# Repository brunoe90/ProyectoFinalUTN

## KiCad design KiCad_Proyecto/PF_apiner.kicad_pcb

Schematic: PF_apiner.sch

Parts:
C35: 0.1uF; c_0402; Digikey# 311-1336-1-ND
D12: MBR0520; SOD-123; Digikey# MBR0520LT1GOSCT-ND
H1, H2, H3, H4: PCB_HOLE; MountingHole_3mm
J1: OBDII Header; YH1012
J2: Conn_01x05; PIN_ARRAY_5x1_1.27_SMD; Digikey# 952-3609-ND

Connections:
+5V: C35.1, D12.2; also elsewhere on the board
+5V_USB: D12.1, J2.1
/HS_CAN_N: J1.14; also elsewhere on the board
/HS_CAN_P: J1.6; also elsewhere on the board
/J1850_BUS+: J1.2; also elsewhere on the board
/J1850_BUS-: J1.10; also elsewhere on the board
/K-LINE: J1.7; also elsewhere on the board
/L-LINE: J1.15; also elsewhere on the board
/MS_CAN_N: J1.11; also elsewhere on the board
/MS_CAN_P: J1.3; also elsewhere on the board
/MicroM4/RESET: J2.4; also elsewhere on the board
/MicroM4/UART0_RX: J2.2; also elsewhere on the board
/MicroM4/UART0_TX: J2.3; also elsewhere on the board
/SW_CAN: J1.1; also elsewhere on the board
GND: C35.2, J1.4, J1.5, J2.5; also elsewhere on the board
VIN: J1.16; also elsewhere on the board

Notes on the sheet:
POWER SUPPLY
OBD II
El UART0 va al USB, el resto hay que configurarlos
agrandar d1

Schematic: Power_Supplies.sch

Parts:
C1: 10nF; c_0603
C2, C3: 0.1uF; c_0402
C4, C6, C7, C9: 47uF; c_1206
C5: 1uF; c_0402
C8: 62pF; c_0402
C10, C11: 10uF; c_0603
D1: RLCAMP0531T9; SOD-123
D2: SBR2U30P1; POWERDI-123
F1: 2A; ptc_1210; Digikey# F2570CT-ND
L1: 10uH; SRN6045
R1: 100k; r_0402
R2: 13,7k; r_0402
U1: TPS54202; SOT-23-6; Digikey# 296-44396-1-ND
U2: AZ1117EH-3.3TRG1; SOT-223

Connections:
+3.3V: C5.1, U2.2; also elsewhere on the board
+5V: C2.1, C8.1, C10.1, C11.1, L1.2, R1.1, U2.3; also elsewhere on the board
GND: C1.2, C2.2, C4.2, C5.2, C6.2, C7.2, C9.2, C10.2, C11.2, D1.1, R2.2, U1.1, U2.1; also elsewhere on the board
unnamed: C3.1, L1.1, U1.2
unnamed: C3.2, U1.6
unnamed: C8.2, R1.2, R2.1, U1.4
VIN: C1.1, F1.1; also elsewhere on the board

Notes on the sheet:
poner infinitas vias data tps #21

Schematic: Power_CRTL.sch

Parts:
Q1: 2N7002; SOT-23; Digikey# 2N7002ET1GOSCT-ND
Q2, Q3: BSS314PE; SOT-23; Digikey# BSS314PE H6327CT-ND
R3, R4: 100k; r_0402; Digikey# 311-100KLRCT-ND

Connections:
+3.3V: R3.1; also elsewhere on the board
+5V: Q3.2; also elsewhere on the board
/MicroM4/PWR_SAVE: Q1.1, R3.2; also elsewhere on the board
DLC_SW: Q2.3; also elsewhere on the board
GND: Q1.2; also elsewhere on the board
unnamed: Q1.3, Q2.1, Q3.1, R4.2

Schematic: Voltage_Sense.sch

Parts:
C12: 0.1uF; c_0402; Digikey# 311-1336-1-ND
D3: BAT54SL; SOT-23; Digikey# BAT54SLT1GOSCT-ND
R5: 62k 1%; r_0402; Digikey# 311-62.0KLRCT-ND
R6: 10K 1%; r_0402; Digikey# 311-10.0KLRCT-ND

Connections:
+3.3V: D3.2; also elsewhere on the board
/OBD_UART_Interface/ANALOG_IN: C12.1, D3.3, R5.1, R6.1; also elsewhere on the board
GND: C12.2, D3.1, R6.2; also elsewhere on the board

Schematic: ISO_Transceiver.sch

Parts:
C13, C14, C15: 0.1uF x 25V; c_0603; Digikey# 311-1341-1-ND
D4, D5: BAT54SL; SOT-23; Digikey# BAT54SLT1GOSCT-ND
Q4, Q5: MMBT3904; SOT-23; Digikey# MMBT3904LT3GOSCT-ND
R7, R13: 1K; r_0402; Digikey# 311-1.0KJRCT-ND
R8, R9, R11, R12: 10K; r_0402; Digikey# 311-10KJRCT-ND
R10, R14: 510 0.5W; r_0805; Digikey# P510ADCT-ND
U3: LM339; TSSOP-14_4.4x5mm_Pitch0.65mm; Digikey# 296-6607-1-ND

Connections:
+3.3V: R12.2; also elsewhere on the board
/ISO_Transceiver/ISO_K_TX: R7.1; also elsewhere on the board
/ISO_Transceiver/ISO_L_TX: R13.1; also elsewhere on the board
/ISO_Transceiver/ISO_RX: R12.1, U3.2; also elsewhere on the board
/K-LINE: D4.3, Q4.3, R10.1, R11.1; also elsewhere on the board
/L-LINE: D5.3, Q5.3, R14.1; also elsewhere on the board
DLC_SW: C15.1, R8.2, R10.2, R14.2, U3.3 (V+); also elsewhere on the board
GND: C13.2, C14.2, C15.2, D4.1, D5.1, Q4.2, Q5.2, R9.1, U3.12 (V-); also elsewhere on the board
unnamed: Q4.1, R7.2
unnamed: Q5.1, R13.2
unnamed: R8.1, R9.2, U3.5 (+)
unnamed: R11.2, U3.4 (-)

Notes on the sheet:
Ubicar cerca del LM339

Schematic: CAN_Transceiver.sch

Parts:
C16, C17: 0.1uF; c_0402; Digikey# 311-1336-1-ND
C18: 10uF 25V; c_0805; Digikey# 587-2985-6-ND
C19, C20, C22, C23: 560 pF; c_0402; Digikey# 311-1029-1-ND
C21: 150 pF; c_0402; Digikey# 490-3229-1-ND
Q6: 2N7002; SOT-23; Digikey# 2N7002ET1GOSCT-ND
R15: 1,5K; r_0402; Digikey# 311-1.50KLRCT-ND
R16: 6,49K; r_0805; Digikey# 311-6.49KCRCT-ND
R17, R19, R22, R24: 100; r_0402; Digikey# 311-100JRCT-ND
R18: 10K; r_0402; Digikey# 311-10KJRCT-ND
R20: 130; r_2512; Digikey# A116011CT-ND
R21, R23: DNP; c_0402; Digikey# 311-120JRCT-ND
U4: MCP25612FD; SOIC-14; Digikey# MCP25612FD-H/SL-ND
U5: TH8056; SOIC-8; Digikey# TH8056KDC-AAA-008-RETR-ND
U6, U7, U8: PESD1CAN; SC-70; Digikey# 568-10731-1-ND

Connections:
+3.3V: R15.2; also elsewhere on the board
/CAN_Transceiver/HS_CAN_RX: U4.4; also elsewhere on the board
/CAN_Transceiver/HS_CAN_TX: U4.1; also elsewhere on the board
/CAN_Transceiver/MS_CAN_RX: U4.8; also elsewhere on the board
/CAN_Transceiver/MS_CAN_TX: U4.5; also elsewhere on the board
/CAN_Transceiver/SW_CAN_LOAD: Q6.1, R18.2; also elsewhere on the board
/CAN_Transceiver/SW_CAN_MODE0: U5.2; also elsewhere on the board
/CAN_Transceiver/SW_CAN_MODE1: U5.3; also elsewhere on the board
/CAN_Transceiver/SW_CAN_RX: R15.1, U5.4; also elsewhere on the board
/CAN_Transceiver/SW_CAN_TX: U5.1; also elsewhere on the board
/HS_CAN_N: R19.2, R21.2, U4.12, U6.1; also elsewhere on the board
/HS_CAN_P: R17.2, R21.1, U4.13, U6.2; also elsewhere on the board
/MS_CAN_N: R23.2, R24.2, U4.9, U8.2; also elsewhere on the board
/MS_CAN_P: R22.2, R23.1, U4.10, U8.1; also elsewhere on the board
/SW_CAN: C21.1, R16.2, R20.2, U5.7, U7.1, U7.2; also elsewhere on the board
GND: C16.1, C17.1, C18.2, C19.2, C20.2, C21.2, C22.2, C23.2, Q6.2, R18.1, U4.2, U4.6, U4.11, U4.14, U5.8, U6.3, U7.3, U8.3; also elsewhere on the board
unnamed: C19.1, R17.1
unnamed: C20.1, R19.1
unnamed: C22.1, R22.1
unnamed: C23.1, R24.1
unnamed: Q6.3, R20.1
unnamed: R16.1, U5.6

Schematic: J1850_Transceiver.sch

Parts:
C24, C25, C26, C27: 0.1uF x 25V; c_0603; Digikey# 311-1341-1-ND
D6, D7: BAT54SL; SOT-23; Digikey# BAT54SLT1GOSCT-ND
D8, D9, D10: DB2J31000L; SOD-323; Digikey# DB2J31000LCT-ND
Q7, Q8, Q10: 2N7002; SOT-23; Digikey# 2N7002ET1GOSCT-ND
Q9: BSS314PE; SOT-23; Digikey# BSS314PE H6327CT-ND
R25: 240; r_0402; Digikey# 311-240LRCT-ND
R26: 866; r_0402; Digikey# YAG3248CT-ND
R27: 374; r_0402; Digikey# YAG3137CT-ND
R28, R29, R30, R31, R32, R33, R35, R36, R37, R38, R39: 10K; r_0402; Digikey# 311-10KJRCT-ND
R34: 2,7K; r_0402; Digikey# 311-2.7KJRCT-ND
U3: LM339; TSSOP-14_4.4x5mm_Pitch0.65mm; Digikey# 296-6607-1-ND
U9: LM317; SOT-89-3; Digikey# 296-26093-1-ND

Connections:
+3.3V: R33.2, R39.2; also elsewhere on the board
/J1850_BUS+: D6.3, D8.2, R30.1, R32.2, R37.1; also elsewhere on the board
/J1850_BUS-: D7.3, Q10.3, R31.1, R38.1; also elsewhere on the board
/J1850_Transceiver/J1850_BUS+_TX: Q8.1, R28.2; also elsewhere on the board
/J1850_Transceiver/J1850_BUS+_VH: Q7.1; also elsewhere on the board
/J1850_Transceiver/J1850_BUS-_TX: Q10.1, R36.1; also elsewhere on the board
/J1850_Transceiver/PWM_RX: R33.1, U3.1; also elsewhere on the board
/J1850_Transceiver/VPW_RX: R39.1, U3.13; also elsewhere on the board
DLC_SW: C25.1, U3.3 (V+), U9.3; also elsewhere on the board
GND: C24.2, C25.2, C26.2, C27.2, D6.1, D7.1, D9.2, Q7.2, Q8.2, Q10.2, R27.1, R28.1, R35.1, U3.12 (V-); also elsewhere on the board
unnamed: D8.1, Q9.3
unnamed: D9.1, R32.1
unnamed: D10.2, R38.2
unnamed: Q7.3, R26.1, R27.2
unnamed: Q8.3, Q9.1, R29.1
unnamed: R25.1, R26.2, U9.1
unnamed: R30.2, U3.7 (+)
unnamed: R31.2, U3.6 (-)
unnamed: R34.1, R35.2, U3.10 (-)
unnamed: R37.2, U3.11 (+)

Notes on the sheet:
revizar este footprint

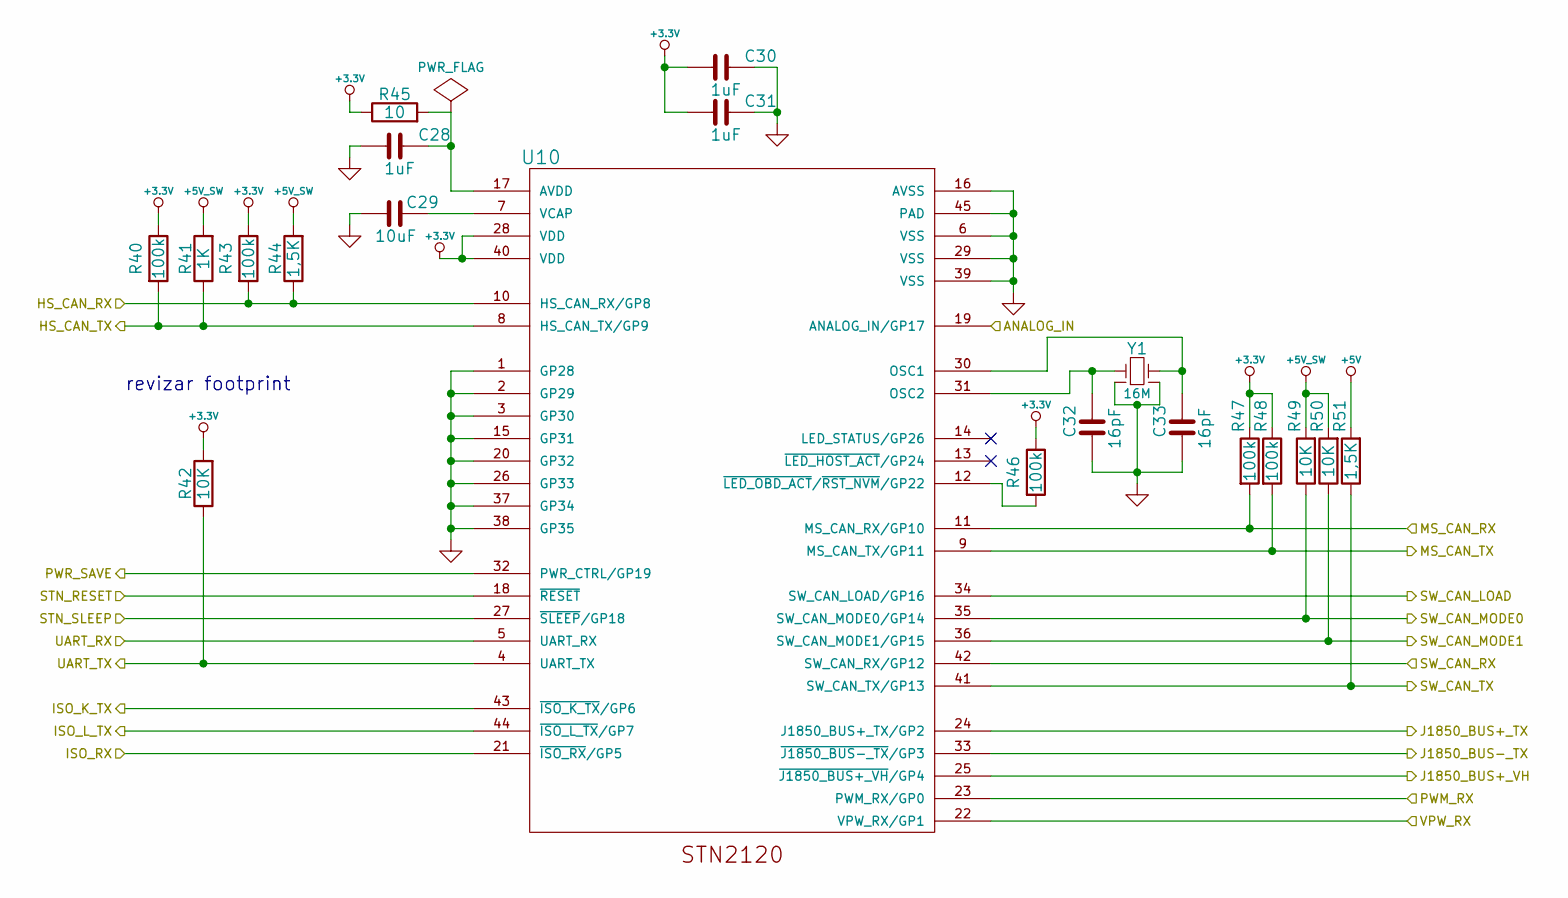
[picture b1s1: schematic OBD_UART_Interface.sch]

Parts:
C28, C30, C31: 1uF; c_0402; Digikey# 587-1231-1-ND
C29: 10uF; c_0603; Digikey# 587-1256-1-ND
C32, C33: 16pF; c_0402; Digikey# 490-5926-1-ND
R40, R43, R46, R47, R48: 100k; r_0402; Digikey# 311-100KLRCT-ND
R41: 1K; r_0402; Digikey# 311-1.0KJRCT-ND
R42: 10K; r_0402; Digikey# 311-1.0KJRCT-ND
R44, R51: 1,5K; r_0402; Digikey# 311-1.50KLRCT-ND
R45: 10; r_0402; Digikey# 311-10JRCT-ND
R49, R50: 10K; r_0402; Digikey# 311-10KJRCT-ND
U10: STN2120; QFN-44-1EP_8x8mm_Pitch0.65mm
Y1: 16M; XTAL_32x25; Digikey# 887-2555-1-ND

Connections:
+3.3V: C30.2, C31.2, R40.1, R42.2, R43.1, R45.1, R46.1, R47.1, R48.1, U10.28 (VDD), U10.40 (VDD); also elsewhere on the board
+5V: R51.2; also elsewhere on the board
/CAN_Transceiver/HS_CAN_RX: R43.2, R44.1, U10.10 (HS_CAN_RX/GP8); also elsewhere on the board
/CAN_Transceiver/HS_CAN_TX: R40.2, R41.1, U10.8 (HS_CAN_TX/GP9); also elsewhere on the board
/CAN_Transceiver/MS_CAN_RX: R47.2, U10.11 (MS_CAN_RX/GP10); also elsewhere on the board
/CAN_Transceiver/MS_CAN_TX: R48.2, U10.9 (MS_CAN_TX/GP11); also elsewhere on the board
/CAN_Transceiver/SW_CAN_LOAD: U10.34 (SW_CAN_LOAD/GP16); also elsewhere on the board
/CAN_Transceiver/SW_CAN_MODE0: R49.1, U10.35 (SW_CAN_MODE0/GP14); also elsewhere on the board
/CAN_Transceiver/SW_CAN_MODE1: R50.1, U10.36 (SW_CAN_MODE1/GP15); also elsewhere on the board
/CAN_Transceiver/SW_CAN_RX: U10.42 (SW_CAN_RX/GP12); also elsewhere on the board
/CAN_Transceiver/SW_CAN_TX: R51.1, U10.41 (SW_CAN_TX/GP13); also elsewhere on the board
/ISO_Transceiver/ISO_K_TX: U10.43 (~ISO_K_TX~/GP6); also elsewhere on the board
/ISO_Transceiver/ISO_L_TX: U10.44 (~ISO_L_TX~/GP7); also elsewhere on the board
/ISO_Transceiver/ISO_RX: U10.21 (~ISO_RX~/GP5); also elsewhere on the board
/J1850_Transceiver/J1850_BUS+_TX: U10.24 (J1850_BUS+_TX/GP2); also elsewhere on the board
/J1850_Transceiver/J1850_BUS+_VH: U10.25 (~J1850_BUS+_VH~/GP4); also elsewhere on the board
/J1850_Transceiver/J1850_BUS-_TX: U10.33 (~J1850_BUS-_TX~/GP3); also elsewhere on the board
/J1850_Transceiver/PWM_RX: U10.23 (PWM_RX/GP0); also elsewhere on the board
/J1850_Transceiver/VPW_RX: U10.22 (VPW_RX/GP1); also elsewhere on the board
/MicroM4/PWR_SAVE: U10.32 (PWR_CTRL/GP19); also elsewhere on the board
/MicroM4/STN_RESET: U10.18 (~RESET); also elsewhere on the board
/MicroM4/STN_SLEEP: U10.27 (~SLEEP~/GP18); also elsewhere on the board
/MicroM4/UART1_RX: R42.1, U10.4 (UART_TX); also elsewhere on the board
/MicroM4/UART1_TX: U10.5 (UART_RX); also elsewhere on the board
/OBD_UART_Interface/ANALOG_IN: U10.19 (ANALOG_IN/GP17); also elsewhere on the board
GND: C28.2, C29.1, C30.1, C31.1, C32.2, C33.2, U10.1 (GP28), U10.2 (GP29), U10.3 (GP30), U10.6 (VSS), U10.15 (GP31), U10.16 (AVSS), U10.20 (GP32), U10.26 (GP33), U10.29 (VSS), U10.37 (GP34), U10.38 (GP35), U10.39 (VSS), U10.45 (PAD), Y1.2, Y1.4; also elsewhere on the board
unnamed: C28.1, R45.2, U10.17 (AVDD)
unnamed: C29.2, U10.7 (VCAP)
unnamed: C32.1, U10.31 (OSC2), Y1.1
unnamed: C33.1, U10.30 (OSC1), Y1.3
unnamed: R46.2, U10.12 (~LED_OBD_ACT~/~RST_NVM~/GP22)

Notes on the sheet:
revizar footprint

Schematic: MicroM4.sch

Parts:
C34, C37, C38: 0.1uF; c_0402; Digikey# 311-1336-1-ND
C36: 10uF; c_0603; Digikey# 587-1256-1-ND
DS1: LED; LED-0603; Digikey# SML-D12U1WT86CT-ND
R52, R54: 10K; r_0402; Digikey# 311-10KJRCT-ND
R53: 100K; l_0402; Digikey# MCS0402-100K-CFCT-ND
R55: 100; r_0402; Digikey# 311-100JRCT-ND
SW1: SW_RESET; TACT_SMD_4.5X4.5; Digikey# EG5350CT-ND
SW2: SW_BOOT; TACT_SMD_4.5X4.5; Digikey# EG5350CT-ND
U14: ESP32-WROOM; Digikey# 1904-1023-1-ND

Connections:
+3.3V: C36.1, C37.1, R52.2, R53.1, R54.2, U14.2; also elsewhere on the board
/MicroM4/BOOT: C34.1, R54.1, SW2.1, SW2.2, U14.25
/MicroM4/Led_Status: R55.2, U14.13
/MicroM4/PWR_SAVE: U14.28; also elsewhere on the board
/MicroM4/RESET: C38.1, R52.1, SW1.1, SW1.2, U14.3; also elsewhere on the board
/MicroM4/STN_RESET: U14.10; also elsewhere on the board
/MicroM4/STN_SLEEP: U14.33; also elsewhere on the board
/MicroM4/UART0_RX: R53.2, U14.34; also elsewhere on the board
/MicroM4/UART0_TX: U14.35; also elsewhere on the board
/MicroM4/UART1_RX: U14.17; also elsewhere on the board
/MicroM4/UART1_TX: U14.18; also elsewhere on the board
GND: C34.2, C38.2, DS1.2 (A), SW1.3, SW1.4, SW2.3, SW2.4, U14.1, U14.14, U14.15, U14.24, U14.38, U14.39; also elsewhere on the board
unnamed: C36.2, C37.2
unnamed: DS1.1 (K), R55.1

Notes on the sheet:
PAG 10 pull-up interno GPIO 0 -> 0: DOWNLOAD BOOT GPIO 0 -> 1: SPI BOOT
PAG 10 GPIO15 -> MTDO-> 0 -> U0TXD Silent dejarlo sin soldar la resistencia y despues poner una de 0 ohm
PAG 15 Figure 5 GPIO12 -> MTDI ->0

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
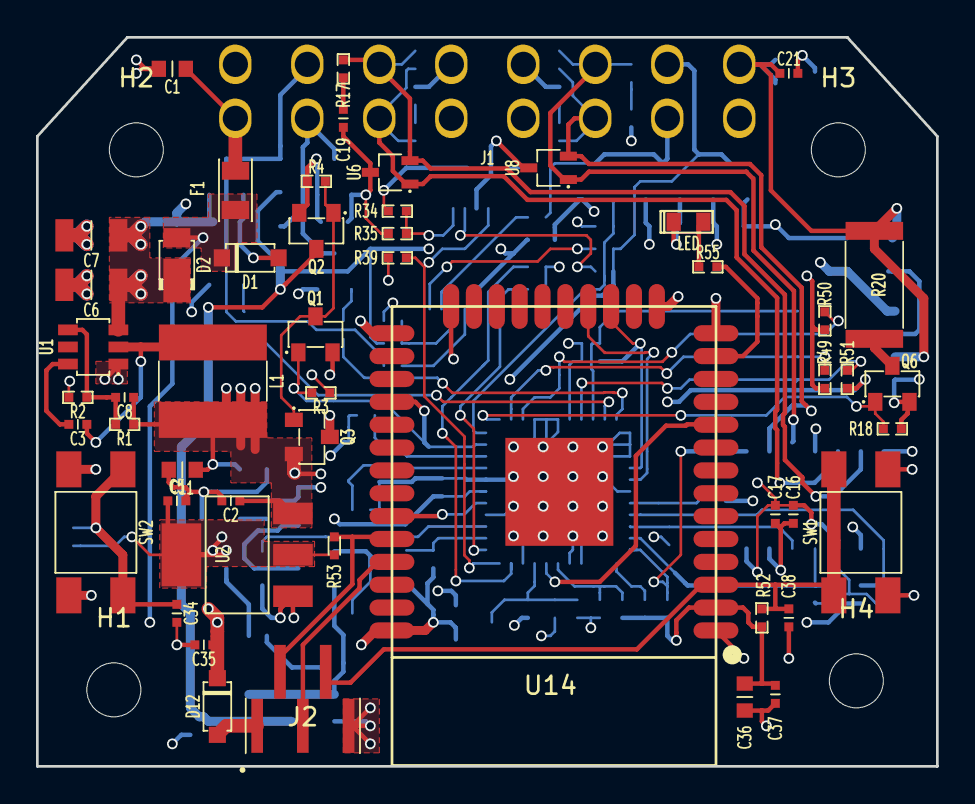
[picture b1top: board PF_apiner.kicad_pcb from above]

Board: 4 copper layers, 50.0 x 40.5 mm, 137 parts (0 on the bottom side), 78 nets.

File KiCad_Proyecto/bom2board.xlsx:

Prj: | PF_apiner.xml |  |  |  |  |  | Board Qty: | 5
Co.: |  |  |  |  |  |  | Unit Cost: | 0
Prj date: | dom 11 ago 2019 18:53:19 -03 |  |  |  |  |  | Total Cost: | 0
$ date: | 2019-08-12 21:58:06
Global Part Info
Refs | Value | Desc | Footprint | Manf | Manf# | Qty | Unit$ | Ext$
C1 | 10nF | CAP CER 10000PF 25V C0G 0603 | chip_rlc:c_0603 | TDK Corporation | 445-2664-1-ND | 5 |  | 0
C10,C11 | 10uF | CAP CER 10UF 6.3V X5R 0603 | chip_rlc:c_0603 | Taiyo Yuden | 587-1256-1-ND | 10 |  | 0
C12,C16,C17,C34,C35,C37,C38 | 0.1uF | CAP CER 0.1UF 10V X5R 0402 | chip_rlc:c_0402 | Yageo | CC0402KRX5R6BB104 | 35 |  | 0
C18 | 10uF 25V | CAP CER 10UF 25V X5R 0805 | chip_rlc:c_0805 | Taiyo Yuden | TMK212BBJ106KG-T | 5 |  | 0
C19,C20,C22,C23 | 560 pF | CAP CER 560PF 50V X7R 0402 | chip_rlc:c_0402 | Yageo | CC0402KRX7R9BB561 | 20 |  | 0
C2,C3 | 0.1uF | CAP CER 0.1UF 10V X5R 0402 | chip_rlc:c_0402 | Yageo | 311-1336-1-ND | 10 |  | 0
C21 | 150 pF | CAP CER 150PF 50V C0G/NP0 0402 | chip_rlc:c_0402 | Murata | GRM1555C1H151JA01D | 5 |  | 0
C28,C30,C31 | 1uF | CAP CER 1UF 6.3V X5R 0402 | chip_rlc:c_0402 | Taiyo Yuden | JMK105BJ105KV-F | 15 |  | 0
C29,C36 | 10uF | CAP CER 10UF 6.3V X5R 0603 | chip_rlc:c_0603 | Taiyo Yuden | JMK107BJ106MA-T | 10 |  | 0
C32,C33 | 16pF | CAP CER 16PF 50V C0G/NP0 0402 | chip_rlc:c_0402 | Murata | GRM1555C1H160JA01D | 10 |  | 0
C4,C6,C7,C9 | 47uF | 47µF ±20% 25V Ceramic Capacitor X5R 1206 (3216 Metric) | chip_rlc:c_1206 | TDK Corporation | 445-8047-1-ND | 20 |  | 0
C5 | 1uF | CAP CER 1UF 6.3V X5R 0402 | chip_rlc:c_0402 | Taiyo Yuden | 587-1231-1-ND | 5 |  | 0
C8 | 62pF | CAP CER 62PF 50V C0G/NPO 0402 | chip_rlc:c_0402 | Yageo | 311-1674-1-ND | 5 |  | 0
C13-C15,C24-C27 | 0.1uF x 25V | CAP CER 0.1UF 25V X7R 0603 | chip_rlc:c_0603 | Yageo | CC0603KRX7R8BB104 | 35 |  | 0
D1 | RLCAMP0531T9 | TVS DIODE 14VWM 23.2VC SOD-123FL | to-sod-sot:SOD-123 | Micro Commercial Co | SMF14A-TPMSCT-ND | 5 |  | 0
D12 | MBR0520 | DIODE SCHOTTKY 20V 500MA SOD123 | to-sod-sot:SOD-123 | ON Semiconductor | MBR0520LT1G | 5 |  | 0
D2 | SBR2U30P1 | DIODE SBR 30V 2A POWERDI123 | to-sod-sot:POWERDI-123 | Diodes Incorporated | SBR2U30P1DICT-ND | 5 |  | 0
D3-D7 | BAT54SL | Diode Array 1 Pair Series Connection Schottky 30V 200mA (DC) Surface Mount TO-2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 | to-sod-sot:SOT-23 | ON Semiconductor | BAT54SLT1G | 25 |  | 0
D8-D10 | DB2J31000L | Diode Schottky 30V 200mA Surface Mount SMini2-F5-B | to-sod-sot:SOD-323 | Panasonic Electronic Components | DB2J31000L | 15 |  | 0
DS1 | LED |  | misc:LED-0603 | Rohm Semiconductor | SML-D12U1WT86 | 5 |  | 0
F1 | 2A | FUSE BOARD MNT 2A 63VAC/VDC 1206 | misc:ptc_1210 | Littelfuse Inc. | 0468002.NR | 5 |  | 0
H1-H4 | PCB_HOLE |  | misc:MountingHole_3mm |  |  | 20 |  | 0
J1 | OBDII Header | OBDII male 90° connector | conn:YH1012 | Yeahui | YH1012 | 5 |  | 0
J2 | Conn_01x05 | CONN HDR 1.27MM SMT AU 5POS | conn:PIN_ARRAY_5x1_1.27_SMD | Harwin Inc. | M50-3630542 | 5 |  | 0
L1 | 10uH | 10µH Shielded Wirewound Inductor 2.5A 58.6 mOhm Max Nonstandard | inductor:SRN6045 | Bourns Inc | SRN6045-100MCT-ND | 5 |  | 0
Q1,Q6-Q8,Q10 | 2N7002 | MOSFET N-CH 60V 260MA SOT-23 | to-sod-sot:SOT-23 | ON Semiconductor | 2N7002ET1G | 25 |  | 0
Q2,Q3,Q9 | BSS314PE | MOSFET P-CH 30V 1.5A SOT23 | to-sod-sot:SOT-23 | Infineon | BSS314PE H6327 | 15 |  | 0
Q4,Q5 | MMBT3904 | TRANS NPN 40V 0.2A SOT23 | to-sod-sot:SOT-23 | ON Semiconductor | MMBT3904LT3G | 10 |  | 0
R1 | 100k | RES SMD 100K OHM 1% 1/16W 0402 | chip_rlc:r_0402 | Yageo | 311-100KLRCT-ND | 5 |  | 0
R10,R14 | 510 0.5W | RES SMD 510 OHM 5% 1/2W 0805 | chip_rlc:r_0805 | Panasonic Electronic Components | ERJ-P06J511V | 10 |  | 0
R15,R44,R51 | 1,5K | RES SMD 1.5K OHM 1% 1/16W 0402 | chip_rlc:r_0402 | Yageo | RC0402FR-071K5L | 15 |  | 0
R16 | 6,49K | RES SMD 6.49K OHM 1% 1/8W 0805 | chip_rlc:r_0805 | Yageo | RC0805FR-076K49L | 5 |  | 0
R17,R19,R22,R24,R55 | 100 | RES SMD 100 OHM 5% 1/16W 0402 | chip_rlc:r_0402 | Yageo | RC0402JR-07100RL | 25 |  | 0
R2 | 13,7k | RES SMD 13.7K OHM 1% 1/16W 0402 | chip_rlc:r_0402 | Yageo | 311-13.7KLRCT-ND | 5 |  | 0
R20 | 130 | RES SMD 130 OHM 1% 2W 2512 | chip_rlc:r_2512 | TE Connectivity | 3521130RFT | 5 |  | 0
R21,R23 | DNP | RES SMD 120 OHM 5% 1/16W 0402 | chip_rlc:c_0402 | Yageo | RC0402JR-07120RL | 10 |  | 0
R25 | 240 | RES SMD 240 OHM 1% 1/16W 0402 | chip_rlc:r_0402 | Yageo | RC0402FR-07240RL | 5 |  | 0
R26 | 866 | RES SMD 866 OHM 1% 1/16W 0402 | chip_rlc:r_0402 | Yaego | RC0402FR-07866RL | 5 |  | 0
R27 | 374 | RES SMD 374 OHM 1% 1/16W 0402 | chip_rlc:r_0402 | Yageo | RC0402FR-07374RL | 5 |  | 0
R3,R4,R40,R43,R46-R48 | 100k | RES SMD 100K OHM 1% 1/16W 0402 | chip_rlc:r_0402 | Yageo | RC0402FR-07100KL | 35 |  | 0
R34 | 2,7K | RES SMD 2.7K OHM 5% 1/16W 0402 | chip_rlc:r_0402 | Yageo | RC0402JR-072K7L | 5 |  | 0
R42 | 10K | RES SMD 1K OHM 5% 1/16W 0402 | chip_rlc:r_0402 | Yageo | RC0402JR-071KL | 5 |  | 0
R45 | 10 | RES SMD 10 OHM 5% 1/16W 0402 | chip_rlc:r_0402 | Yageo | RC0402JR-0710RL | 5 |  | 0
R5 | 62k 1% | RES SMD 62K OHM 1% 1/16W 0402 | chip_rlc:r_0402 | Yageo | RC0402FR-0762KL | 5 |  | 0
R53 | 100K | RES SMD 100K OHM 1% 1/10W 0402 | chip_rlc:l_0402 | Vishay Beyschlag | MCS04020C1003FE000 | 5 |  | 0
R6 | 10K 1% | RES SMD 10K OHM 1% 1/16W 0402 | chip_rlc:r_0402 | Yaego | RC0402FR-0710KL | 5 |  | 0
R7,R13,R41 | 1K | RES SMD 1K OHM 5% 1/16W 0402 | chip_rlc:r_0402 | Yageo | RC0402JR-071KL | 15 |  | 0
R8,R9,R11,R12,R18,R28-R33,R35-R39,R49,R50,R52,R54 | 10K | RES SMD 10K OHM 5% 1/16W 0402 | chip_rlc:r_0402 | Yageo | RC0402JR-0710KL | 100 |  | 0
SW1 | SW_RESET | Tactile Switch SPST-NO Top Actuated Surface Mount | misc:TACT_SMD_4.5X4.5 | E-Switch | TL3305AF160QG | 5 |  | 0
SW2 | SW_BOOT | Tactile Switch SPST-NO Top Actuated Surface Mount | misc:TACT_SMD_4.5X4.5 | E-Switch | TL3305AF160QG | 5 |  | 0
U1 | TPS54202 | Buck Switching Regulator IC Positive Adjustable 0.596V 1 Output 2A SOT-23-6 Thi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 | to-sod-sot:SOT-23-6 | Texas Instruments | TPS54202DDCT | 5 |  | 0
U10 | STN2120 | OBD-II, SW-CAN, MS-CAN Interpreter IC | dfn-qfn:QFN-44-1EP_8x8mm_Pitch0.65mm | OBD Solutions | STN2120 | 5 |  | 0
U14 | ESP32-WROOM | WIFI MODULE 32MBITS SPI FLASH | ESP32-footprints-Lib:ESP32-WROOM | Espressif Systems | ESP32-WROOM-32D | 5 |  | 0
U2 | AZ1117EH-3.3TRG1 | IC REG LDO 3.3V 1A SOT223 | to-sod-sot:SOT-223 | Diodes Incorporated | AZ1117EH-3.3TRG1DICT-ND | 5 |  | 0
U3 | LM339 | IC QUAD DIFF COMPARATOR 14-TSSOP | soic-sop-tssop:TSSOP-14_4.4x5mm_Pitch0.65mm | Texas Instruments | LM339PWR | 5 |  | 0
U4 | MCP25612FD | IC TRANSCEIVER CAN HI-SPD 14SOIC | soic-sop-tssop:SOIC-14 | Microchip | MCP25612FD-H/SL | 5 |  | 0
U5 | TH8056 | IC TXRX CAN 8SOIC | soic-sop-tssop:SOIC-8 | Melexis | TH8056KDC-AAA-008-RE | 5 |  | 0
U9 | LM317 | IC REG LINEAR ADJ 0.1A SOT89-3 | to-sod-sot:SOT-89-3 | Texas Instruments | LM317LCPK | 5 |  | 0
U6-U8 | PESD1CAN | TVS DIODE 24VWM 50VC SC70 | to-sod-sot:SC-70 | NXP USA Inc | PESD1CAN-UX | 15 |  | 0
Y1 | 16M | CRYSTAL 16.0000MHZ 8PF SMD | xtal-res-osc:XTAL_32x25 | TXC | 7M-16.000MAHV-T | 5 |  | 0
KiCost\N{REGISTERED SIGN} v.1.1

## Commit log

2018-05-16 first commit .gitignore
2018-05-16 PF_APINER
2018-05-16 removed .bak
2018-05-22 added ATMEGA uC DATASHEET
2018-05-23 added uC
2018-06-12 ready for first rev
2018-06-13 fixed some ports errors
2018-06-18 Se ordeno este quilombo
2018-06-19 Japon de mierda me cagaste el Prode, la fafafa no ayudó
2018-06-19 git commit -m se usa para dejar un mensaje al commitear
2018-06-19 mensaje generado de forma aleatoria
2018-06-24 Esto es un comentario escrito en una consola
2018-07-23 added some footprints
2018-08-15 se agrego la app mobile
2018-08-16 esto me tiene para el cachetazo
2018-09-03 added fusion ready for check
2018-09-04 added Makefile -> clean
2018-09-04 fixed(temp) library problem
2018-09-04 hice un commit y lo estoy subiendo al repositorio
2018-09-04 added dual row smd header and 3.3V
2018-09-06 un cambio que no me acuerdo
2018-09-06 added last footprint
2018-09-11 chupala
2018-09-14 arreglado el merge
2018-09-14 arreglando manquiadas
2018-09-21 cambios boludos
2018-09-26 agregado los datos de la placa
2018-09-26 espero q nada se rompa
2018-09-26 Agregando archivos de la placa.
2018-10-07 se agregaron componentes
2018-10-08 saque el material de mas
2018-10-08 cambiado K a 10.2
2018-10-11 se modificaron cosas, que cosas?, maravillosas
2018-10-11 The Offspring Americana
2018-10-11 agregado placa w=344um
2018-10-16 prog manual + UART cfg
2018-10-18 fixed fuse & wrong fields
2018-10-18 wii arrancamos la rev de footprint
2018-10-18 instanciacion de footprint
2018-10-19 added screw holes
2018-10-25 ME curbas PF pos pcb
2018-10-29 revisen guachos
2018-10-30 def puntas
2018-11-01 version final
2018-11-01 saque archivos de mas
2018-11-02 modificado pcb
2018-11-02 Borrando basura (bruno)
2018-11-02 renombrando folder mas ter
2018-11-06 placa final .dxf
2018-11-06 listo pero dudas
2018-11-06 ahora si papa
2018-11-09 se viene
2018-11-09 es viernes
2018-11-12 Se modifico los nombres por partes del proyecto
2018-11-12 Se subio documentacion que no estaba en el REP0
2018-11-15 se envió Data al repositorio de GIT
2018-11-16 CST terminado falta el crack para completar la simulacion
2018-11-16 Se agrego una pic de la placa
2018-11-17 se hizo el guiso
2018-11-19 PPT.
2018-11-20 ruteado terminado listo para rev
2018-11-21 Agregando PPT.
2018-11-22 le commite
2018-11-22 se comela pablo
2018-11-22 fotos filmina + arreglo
2018-11-22 fotos placa cnc
2018-11-22 fotos mediciones
2018-11-22 datos crudos mediciones
2018-11-22 Actualizando PPT.
2018-12-07 Giladas
2018-12-17 Agregando informe. Falta terminar.
2018-12-17 Cambios.
2018-12-18 Adding latex files.
2018-12-18 Avanzando con informe.
2018-12-18 Correcciones.
2018-12-18 Finalizando informe.
2019-04-06 lalala
2019-08-05 agregado cap en boton, status led y sacado cobre en antena
2019-08-05 arreglado merge
2019-08-05 LISTO PAPA
2019-08-06 actualizado make clean y sacado archivos de mas
2019-08-07 todos los .sch arreglados
2019-08-07 .net y pcb final
2019-08-07 sin querer saque este archivo
2019-08-11 se agregaron el bom con el part number de digikey
2019-08-11 gerber para mandar
2019-08-11 agregado valor a la R
2019-08-22 se agrego el xlsx y el gerber
2019-09-17 added relative path to libs
2022-06-02 Bump @angular/core from 5.2.11 to 11.0.5 in /Mobile App/AutoDiagnostic
    Bumps [@angular/core](https://github.com/angular/angular/tree/HEAD/packages/core) from 5.2.11 to 11.0.5.
    - [Release notes](https://github.com/angular/angular/releases)
    - [Changelog](https://github.com/angular/angular/blob/main/CHANGELOG.md)
    - [Commits](https://github.com/angular/angular/commits/11.0.5/packages/core)
    ---
    updated-dependencies:
2022-11-09 Bump loader-utils from 1.1.0 to 1.4.1 in /Mobile App/AutoDiagnostic
    Bumps [loader-utils](https://github.com/webpack/loader-utils) from 1.1.0 to 1.4.1.
    - [Release notes](https://github.com/webpack/loader-utils/releases)
    - [Changelog](https://github.com/webpack/loader-utils/blob/v1.4.1/CHANGELOG.md)
    - [Commits](https://github.com/webpack/loader-utils/compare/v1.1.0...v1.4.1)
    ---
    updated-dependencies:
2022-11-16 Bump loader-utils from 1.1.0 to 1.4.2 in /Mobile App/AutoDiagnostic
    Bumps [loader-utils](https://github.com/webpack/loader-utils) from 1.1.0 to 1.4.2.
    - [Release notes](https://github.com/webpack/loader-utils/releases)
    - [Changelog](https://github.com/webpack/loader-utils/blob/v1.4.2/CHANGELOG.md)
    - [Commits](https://github.com/webpack/loader-utils/compare/v1.1.0...v1.4.2)
    ---
    updated-dependencies:
2022-12-02 Bump decode-uri-component in /Mobile App/AutoDiagnostic
    Bumps [decode-uri-component](https://github.com/SamVerschueren/decode-uri-component) from 0.2.0 to 0.2.2.
    - [Release notes](https://github.com/SamVerschueren/decode-uri-component/releases)
    - [Commits](https://github.com/SamVerschueren/decode-uri-component/compare/v0.2.0...v0.2.2)
    ---
    updated-dependencies:
    - dependency-name: decode-uri-component
2022-12-07 Bump qs, cordova-browser and express in /Mobile App/AutoDiagnostic
    Bumps [qs](https://github.com/ljharb/qs) to 6.11.0 and updates ancestor dependencies [qs](https://github.com/ljharb/qs), [qs](https://github.com/ljharb/qs), [cordova-browser](https://github.com/apach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
    Updates `qs` from 6.3.2 to 6.11.0
    - [Release notes](https://github.com/ljharb/qs/releases)
    - [Changelog](https://github.com/ljharb/qs/blob/main/CHANGELOG.md)
    - [Commits](https://github.com/ljharb/qs/compare/v6.3.2...v6.11.0)
    Updates `qs` from 6.5.1 to 6.11.0
2022-12-08 Bump express and cordova-browser in /Mobile App/AutoDiagnostic
    Bumps [express](https://github.com/expressjs/express) to 4.18.2 and updates ancestor dependency [cordova-browser](https://github.com/apache/cordova-browser). These dependencies need to be updated tog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
    Updates `express` from 4.16.3 to 4.18.2
    - [Release notes](https://github.com/expressjs/express/releases)
    - [Changelog](https://github.com/expressjs/express/blob/master/History.md)
    - [Commits](https://github.com/expressjs/express/compare/4.16.3...4.18.2)
    Updates `cordova-browser` from 5.0.4 to 6.0.0
2023-02-28 Bump minimist and mkdirp in /Mobile App/AutoDiagnostic
    Bumps [minimist](https://github.com/minimistjs/minimist) and [mkdirp](https://github.com/isaacs/node-mkdirp). These dependencies needed to be updated together.
    Updates `minimist` from 1.2.0 to 1.2.8
    - [Release notes](https://github.com/minimistjs/minimist/releases)
    - [Changelog](https://github.com/minimistjs/minimist/blob/main/CHANGELOG.md)
    - [Commits](https://github.com/minimistjs/minimist/compare/v1.2.0...v1.2.8)
    Updates `mkdirp` from 0.5.1 to 0.5.6
